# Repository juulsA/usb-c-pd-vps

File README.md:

# USB-C-PD-VPS

- variable powersupply driven by USB-PD 
- modular, up to 4 channels
- each channel is isolated
- output voltage 0 - 32V
  - resolution 0.5mV/step
  - voltage correction via sensing pins up to 1V above internally set output voltage
- current sense
  - "fuse" mode
  - current limiting mode
- remote control via USB

## Power Supply Channel Concept

## STM32 Pinout

| Pin Number | Pin Name | Net Name | Description |
| -------- | ------- | ------- | ------- |
| 1 | PB9 | - | - |
| 2 | PC14 | OSCX_IN | - |
| 3 | PC14 | OSCX_OUT | - |
| 4 | VDD | - | - |
| 5 | VSS | - | - |
| 6 | PF2 | NRST | hardware reset |
| 7  | PA0 | ADC0 | secondary side voltage monitoring |
| 8 | PA1 | - | - |
| 9 | PA2 | - | - |
| 10 | PA3 | ADC_SPI_NSS | adc chip select |
| 11 | PA4 | DAC_SPI_NSS | dac chip select |
| 12 | PA5 | STM32_SPI_SCK | spi clock |
| 13 | PA6 | STM32_SPI_MISO | master input/slave output |
| 14 | PA7 | STM32_SPI_MOSI | master output/slave input |
| 15 | PB0 | - | -|
| 16 | PB1 | - | -|
| 17 | PB2 | - | - |
| 18 | PA8 | - | - |
| 19 | PA9 | STM32_UART_TX | uart for controlling/programming |
| 20 | PC6 | - | - |
| 21 | PA10 | STM32_UART_RX | uart for controlling/programming |
| 22 | PA11 | - | - |
| 23 | PA12 | - | - |
| 24 | PA13 | SWDIO | - |
| 25 | PA14 | SWCLK/BOOT0 | enable stm bootloader |
| 26 | PA15 | STM32_TIM1_CH1_PWM | setting preregulator voltage |
| 27 | PB3 | DISABLE_VOLTAGE_SENSING | the external sense pins are not considered in output voltage adjustment  |
| 28 | PB4 | FUSE/#CURRENT_LIMITING_MODE | output is disabled, if an overcurrent event occurs or current is limited by reducing output voltage |
| 29 | PB5 | FPWM/#PFM | fixed frequency or phase frequency mode |
| 30 | PB6 | ENABLE_PWR_SPL | enable switching regulator |
| 31 | PB7 | PG | power good of switching regulator |
| 32 | PB8 | ENABLE_OUTPUT | voltage is applied to the output pins |

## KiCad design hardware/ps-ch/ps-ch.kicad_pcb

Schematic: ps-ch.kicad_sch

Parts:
C1, C4, C5, C8, C16, C17, C18, C25, C26, C27, C28, C29, C30, C33: 0.1μF 0603 100Vdc X7R ±20%; C_0603_1608Metric; Manufacturer Part Number GRM188R72A104MA35
C2, C9: 10pF 0603 100Vdc C0G ±5%; C_0603_1608Metric; Manufacturer Part Number GCM1885C2A100JA16
C3, C10, C12, C13, C14, C15, C19, C20, C21, C22: 10μF 1210 100Vdc X7S ±20%; C_1210_3225Metric; Manufacturer Part Number GRM32EC72A106ME05
C6, C7: 0.1μF 0603 100Vdc X7R ±20%; C_0805_2012Metric; Manufacturer Part Number GRM21BR61H106ME43
C11, C23: 39µF; CP_Elec_8x11.9; Manufacturer Part Number 875075855005
C24: 1μF 0603 16Vdc X7R ±20%; C_0603_1608Metric; Manufacturer Part Number GCM188R71C105MA49
C31, C32: 10μF 0805 50Vdc X5R ±20%; C_0805_2012Metric; Manufacturer Part Number GRM21BR61H106ME43
D1: PMEG60T30ELR; Nexperia_CFP3_SOD-123W; Manufacturer Part Number PMEG60T30ELRX
H1, H2, H3, H4: MountingHole_Pad; MountingHole_3.2mm_M3_Pad
J1, J3: 09652028; Manufacturer Part Number 09652028
J2, J4: Conn_02x12_Odd_Even; PinHeader_2x12_P2.54mm_Vertical
K1: TX2SA-3V; ATX203SA; Manufacturer Part Number TX2SA-3V
L1, L7: 60Ω@100MHz; L_0603_1608Metric; Manufacturer Part Number 74279228600
L2: 33µH; WE-LQS_6045; Manufacturer Part Number 74404064330
L3, L6: 100Ω@100MHz; WE-MPSB_2220; Manufacturer Part Number 74279224101
L4: 1µH; WE-HCI_5040; Manufacturer Part Number 744316100
L5: 2.6µH; WE-HCI_1890; Manufacturer Part Number 7443556260
Q1, Q2: BSS138; SOT-23
R1: 75kΩ 0603 0.1W ±1% ±100ppm/°C; R_0603_1608Metric; Manufacturer Part Number AC0603FR-0775KL
R2: 27kΩ 0603 0.1W ±0.1% ±25ppm/°C; R_0603_1608Metric; Manufacturer Part Number RT0603BRD0727KL
R3: 24kΩ 0603 0.1W ±1% ±100ppm/°C; R_0603_1608Metric; Manufacturer Part Number AC0603FR-0724KL; not fitted
R4: 24kΩ 0603 0.1W ±1% ±100ppm/°C; R_0603_1608Metric; Manufacturer Part Number AC0603FR-0724KL
R5: 3kΩ 0603 0.1W ±0.1% ±25ppm/°C; R_0603_1608Metric; Manufacturer Part Number RT0603BRD073KL
R6: 130kΩ 0603 0.1W ±0.1% ±25ppm/°C; R_0603_1608Metric; Manufacturer Part Number RT0603BRD07130KL
R7: 130kΩ 0603 0.1W ±0.1% ±25ppm/°C; R_0603_1608Metric; Manufacturer Part Number RT0603BRD07130KL; not fitted
R8, R9: 510Ω 1206 0.25W ±1% ±100ppm/°C; R_1206_3216Metric; Manufacturer Part Number AC1206FR-07510RL
R10: 0Ω 0603 0.1W ±1% ±100ppm/°C; R_0603_1608Metric; Manufacturer Part Number AC0603FR-070RL
R11: 4.7kΩ 0603 0.1W ±1% ±100ppm/°C; R_0603_1608Metric; Manufacturer Part Number AC0603FR-074k7L
R12: 10kΩ 0603 0.1W ±1% ±100ppm/°C; R_0402_1005Metric; Manufacturer Part Number AC0402FR-0710KL
R13, R21, R24: 10kΩ 0603 0.1W ±1% ±100ppm/°C; R_0603_1608Metric; Manufacturer Part Number AC0603FR-0710KL
R14: 7.15kΩ 0603 0.1W ±0.1% ±25ppm/°C; R_0603_1608Metric; Manufacturer Part Number RT0603BRD077K15L
R15: 7.15kΩ 0603 0.1W ±0.1% ±25ppm/°C; R_0603_1608Metric; Manufacturer Part Number RT0603BRD077K15L; not fitted
R16: 10kΩ 0603 0.1W ±0.1% ±25ppm/°C; R_0603_1608Metric; Manufacturer Part Number RT0603BRD0710KL
R17: 10kΩ 0603 0.1W ±0.1% ±25ppm/°C; R_0603_1608Metric; Manufacturer Part Number RT0603BRD0710KL; not fitted
R18, R25: 10kΩ 0402 0.063W ±1% ±100ppm/°C; R_0402_1005Metric; Manufacturer Part Number AC0402FR-0710KL
R19, R20: 0Ω 0402 0.063W ±1% ±100ppm/°C; R_0402_1005Metric; Manufacturer Part Number AC0402FR-070RL
R22, R23: 22Ω 0402 0.063W ±1% ±100ppm/°C; R_0402_1005Metric; Manufacturer Part Number AC0402FR-0722RL
U1: LMR51610X; SOT-23-6
U2: LM61495; VQFN-HR(16); Manufacturer Part Number LM61495RPHR
U3, U4: ADuM1401xRW; SOIC-16W_7.5x10.3mm_P1.27mm
U5: OPA992IDBVR; SOT-23-5; Manufacturer Part Number OPA992IDBVR

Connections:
3V3: C25.2, C29.2, J2.1, J2.4, J4.1, J4.4, R21.2, U3.10 (VE2), U3.16 (VDD2), U4.1 (VDD1), U4.7 (VE1)
+3V3: C2.2, C5.2, C6.2, C7.2, C26.2, C27.2, C28.2, C30.2, D1.1 (K), K1.1, L2.1, R1.1, R12.1, U2.5 (BIAS), U3.1 (VDD1), U3.7 (VE1), U4.10 (VE2), U4.16 (VDD2); also elsewhere on the board
/AIN0: R2.1, R5.2; also elsewhere on the board
/Current Measurement/IN: C23.1, L3.1, L6.1, R8.2, R9.2; also elsewhere on the board
/DAC/VOUTA: U5.3 (+); also elsewhere on the board
/DISCHARGE: Q1.1 (G), R25.2; also elsewhere on the board
/EN_PWR_SPL: R18.2, U2.13 (EN); also elsewhere on the board
/Flyback Converter/V_PREREG_EQUIV_PWM: U3.14 (VOA); also elsewhere on the board
/PG: R12.2, U2.10 (~RESET); also elsewhere on the board
/STM32/EN_EXT_VSENSE: Q2.1 (G); also elsewhere on the board
/STM32/STM32_TIM1_CH1_PWM: U3.3 (VIA); also elsewhere on the board
/STM32/STM32_UART_RX: R22.2; also elsewhere on the board
/STM32/STM32_UART_TX: U4.11 (VID); also elsewhere on the board
/STM32/SWCLK/BOOT0: U4.13 (VOB); also elsewhere on the board
/STM32/~STM32_RST: U4.14 (VOA); also elsewhere on the board
/Switch/ARM_OUTPUT: U3.6 (VOD); also elsewhere on the board
/Voltage Correction/VFB: R6.2, R7.2, R11.2, R14.2, R15.2, R16.2, R17.1, U2.7 (FB); also elsewhere on the board
/Voltage Correction/VSENSE+: K1.4; also elsewhere on the board
/Voltage Correction/VSENSE-: K1.9; also elsewhere on the board
ACTIVATE_BOOTLOADER: J2.5, J4.5, R24.2, U4.4 (VIB)
ARM_OUTPUT: R13.2, U3.11 (VID)
Earth: C25.1, C29.1, H1.1, H2.1, H3.1, H4.1, J1.2, J2.2, J2.3, J2.6, J2.7, J2.10, J2.11, J2.14, J2.15, J2.18, J2.19, J2.22, J2.23, J3.2, J4.2, J4.3, J4.6, J4.7, J4.10, J4.11, J4.14, J4.15, J4.18, J4.19, J4.21, J4.22, J4.23, J4.24, R13.1, R24.1, U3.9 (GND2), U3.15 (GND2), U4.2 (GND1), U4.8 (GND1); also elsewhere on the board
GND: C3.1, C4.1, C5.1, C6.1, C7.1, C10.1, C11.2, C12.1, C13.1, C14.1, C15.1, C16.1, C17.1, C18.1, C19.1, C20.1, C21.1, C22.1, C23.2, C24.1, C26.1, C27.1, C28.1, C30.1, C31.1, C32.1, C33.1, K1.10, Q1.2 (S), Q2.2 (S), R3.2, R4.2, R5.1, R14.1, R15.1, R18.1, R19.2, R20.1, R25.1, U1.2 (GND), U2.1 (PGND2), U2.8 (AGND), U2.15 (PGND1), U3.2 (GND1), U3.8 (GND1), U4.9 (GND2), U4.15 (GND2), U5.2 (V-); also elsewhere on the board
NRST: J2.8, J4.8, R21.1, U4.3 (VIA)
unnamed: C9.1, R11.1
unnamed: C9.2, C18.2, C19.2, C20.2, C21.2, C22.2, L3.2, L5.1, L6.2, R6.1, R7.1
unnamed: D1.2 (A), K1.12, Q2.3 (D)
unnamed: Q1.3 (D), R8.1, R9.1
unnamed: C1.1, U1.1 (CB)
unnamed: C3.2, C4.2, L1.1, U1.4 (EN), U1.5 (VIN)
unnamed: C2.1, R1.2, R3.1, R4.1, U1.3 (FB)
unnamed: C1.2, L2.2, U1.6 (SW)
unnamed: C8.1, R10.1, U2.4 (CBOOT)
unnamed: R10.2, U2.3 (RBOOT)
unnamed: R20.2, U2.9 (RT)
unnamed: R19.1, U2.11 (SPSP)
unnamed: C8.2, L5.2, U2.16 (SW)
unnamed: C24.2, U2.6 (VCC), U2.12 (SYNC/MODE)
unnamed: C11.1, C12.2, C13.2, C14.2, C15.2, C16.2, C17.2, L4.1, U2.2 (VIN2), U2.14 (VIN1)
unnamed: R22.1, U4.12 (VOC)
unnamed: R23.2, U4.6 (VOD)
unnamed: R16.1, R17.2, U5.1, U5.4 (-)
unnamed: C32.2, C33.2, L7.1, U5.5 (V+)
PRI_HI: J1.1, J3.1; also elsewhere on the board
UART0_RX: J2.12, R23.1
UART0_TX: J2.9, U4.5 (VIC)
UART1_RX: J2.16, J4.12
UART1_TX: J2.13, J4.9
UART2_RX: J2.20, J4.16
UART2_TX: J2.17, J4.13
UART3_RX: J2.24, J4.20
UART3_TX: J2.21, J4.17
VDC: C10.2, C31.2, L1.2, L4.2, L7.2; also elsewhere on the board
VOUT: K1.3, R2.2; also elsewhere on the board
VSENSE+: K1.5
VSENSE-: K1.8

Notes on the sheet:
7.6uF@5V(-20%) 3uF@35V(-20%)
programmable current limit
INPUT
OPAMP POWER SUPPLY
OUTPUT
5V to 35V
-connect RT(9) to GND for 2.2MHz operation -connect SYNC/MODE(12) to VCC for FPWM -connect SPSP to GND to disable spread-spectrum
0V to 32V
ADC CH0

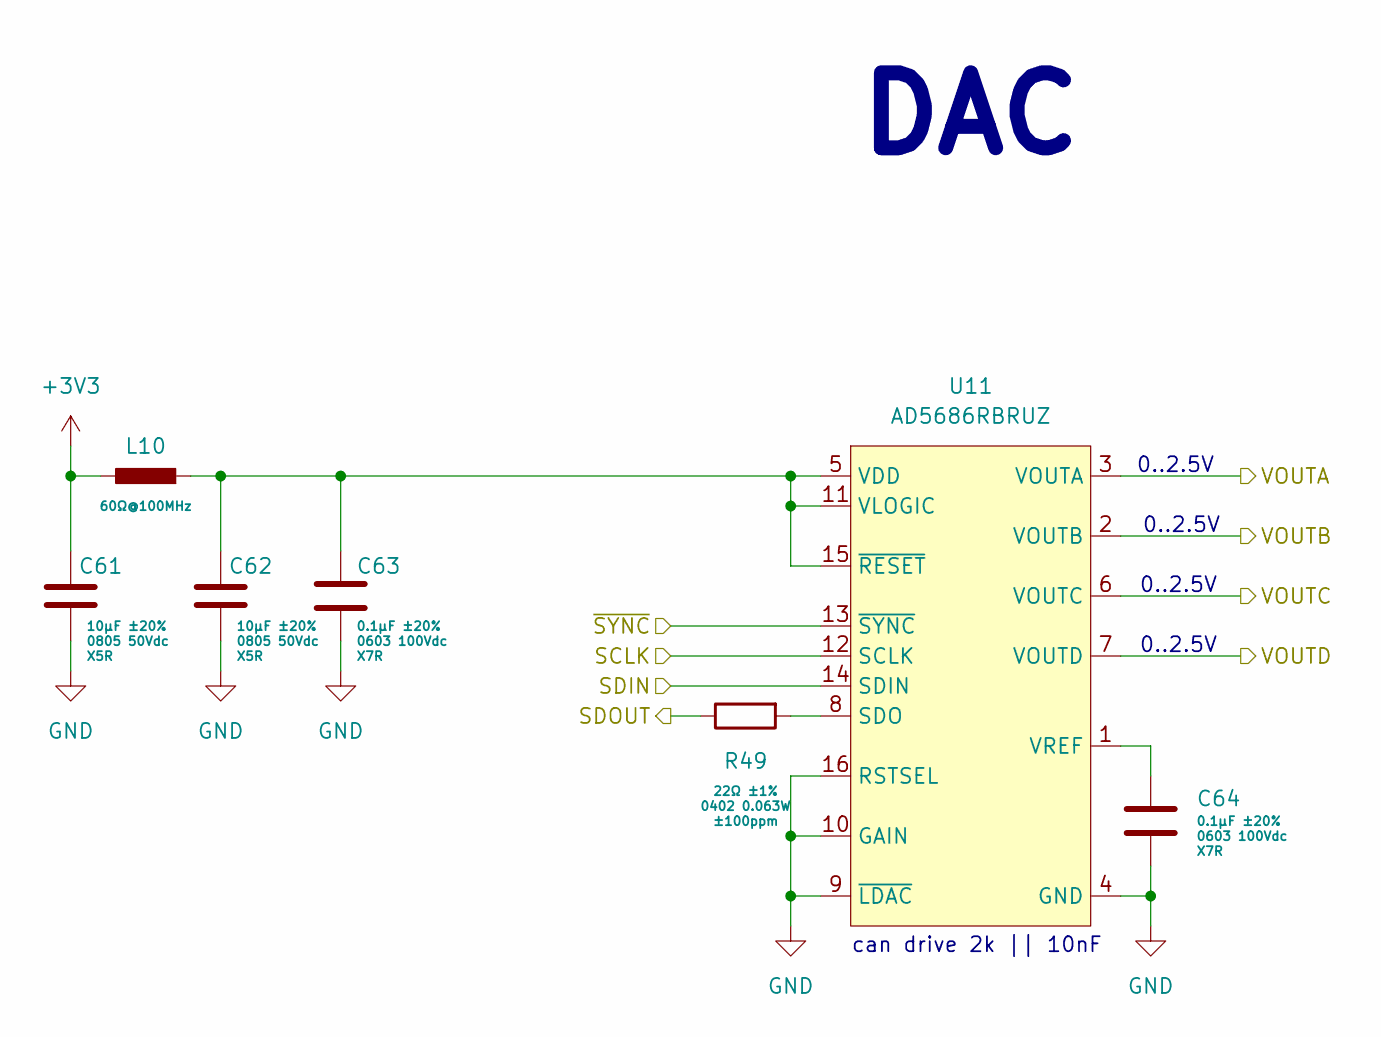
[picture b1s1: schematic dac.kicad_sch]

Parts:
C61, C62: 10μF 0805 50Vdc X5R ±20%; C_0805_2012Metric; Manufacturer Part Number GRM21BR61H106ME43
C63, C64: 0.1μF 0603 100Vdc X7R ±20%; C_0603_1608Metric; Manufacturer Part Number GRM188R72A104MA35
L10: 60Ω@100MHz; L_0603_1608Metric; Manufacturer Part Number 74279228600
R49: 22Ω 0402 0.063W ±1% ±100ppm/°C; R_0402_1005Metric; Manufacturer Part Number AC0402FR-0722RL
U11: AD5686RBRUZ; TSSOP-16_4.4x5mm_P0.65mm; Manufacturer Part Number AD5686RBRUZ-RL7

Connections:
+3V3: C61.2, L10.2; also elsewhere on the board
/ADC_REF: U11.7 (VOUTD); also elsewhere on the board
/Current Measurement/LIMIT: U11.6 (VOUTC); also elsewhere on the board
/DAC/VOUTA: U11.3 (VOUTA); also elsewhere on the board
/DAC/VOUTB: U11.2 (VOUTB); also elsewhere on the board
/MISO: R49.1; also elsewhere on the board
/MOSI: U11.14 (SDIN); also elsewhere on the board
/SCK: U11.12 (SCLK); also elsewhere on the board
/~DAC_CS: U11.13 (~SYNC); also elsewhere on the board
GND: C61.1, C62.1, C63.1, C64.1, U11.4 (GND), U11.9 (~LDAC), U11.10 (GAIN), U11.16 (RSTSEL); also elsewhere on the board
unnamed: R49.2, U11.8 (SDO)
unnamed: C62.2, C63.2, L10.1, U11.5 (VDD), U11.11 (VLOGIC), U11.15 (~RESET)
unnamed: C64.2, U11.1 (VREF)

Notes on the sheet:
0..2.5V
DAC
can drive 2k || 10nF

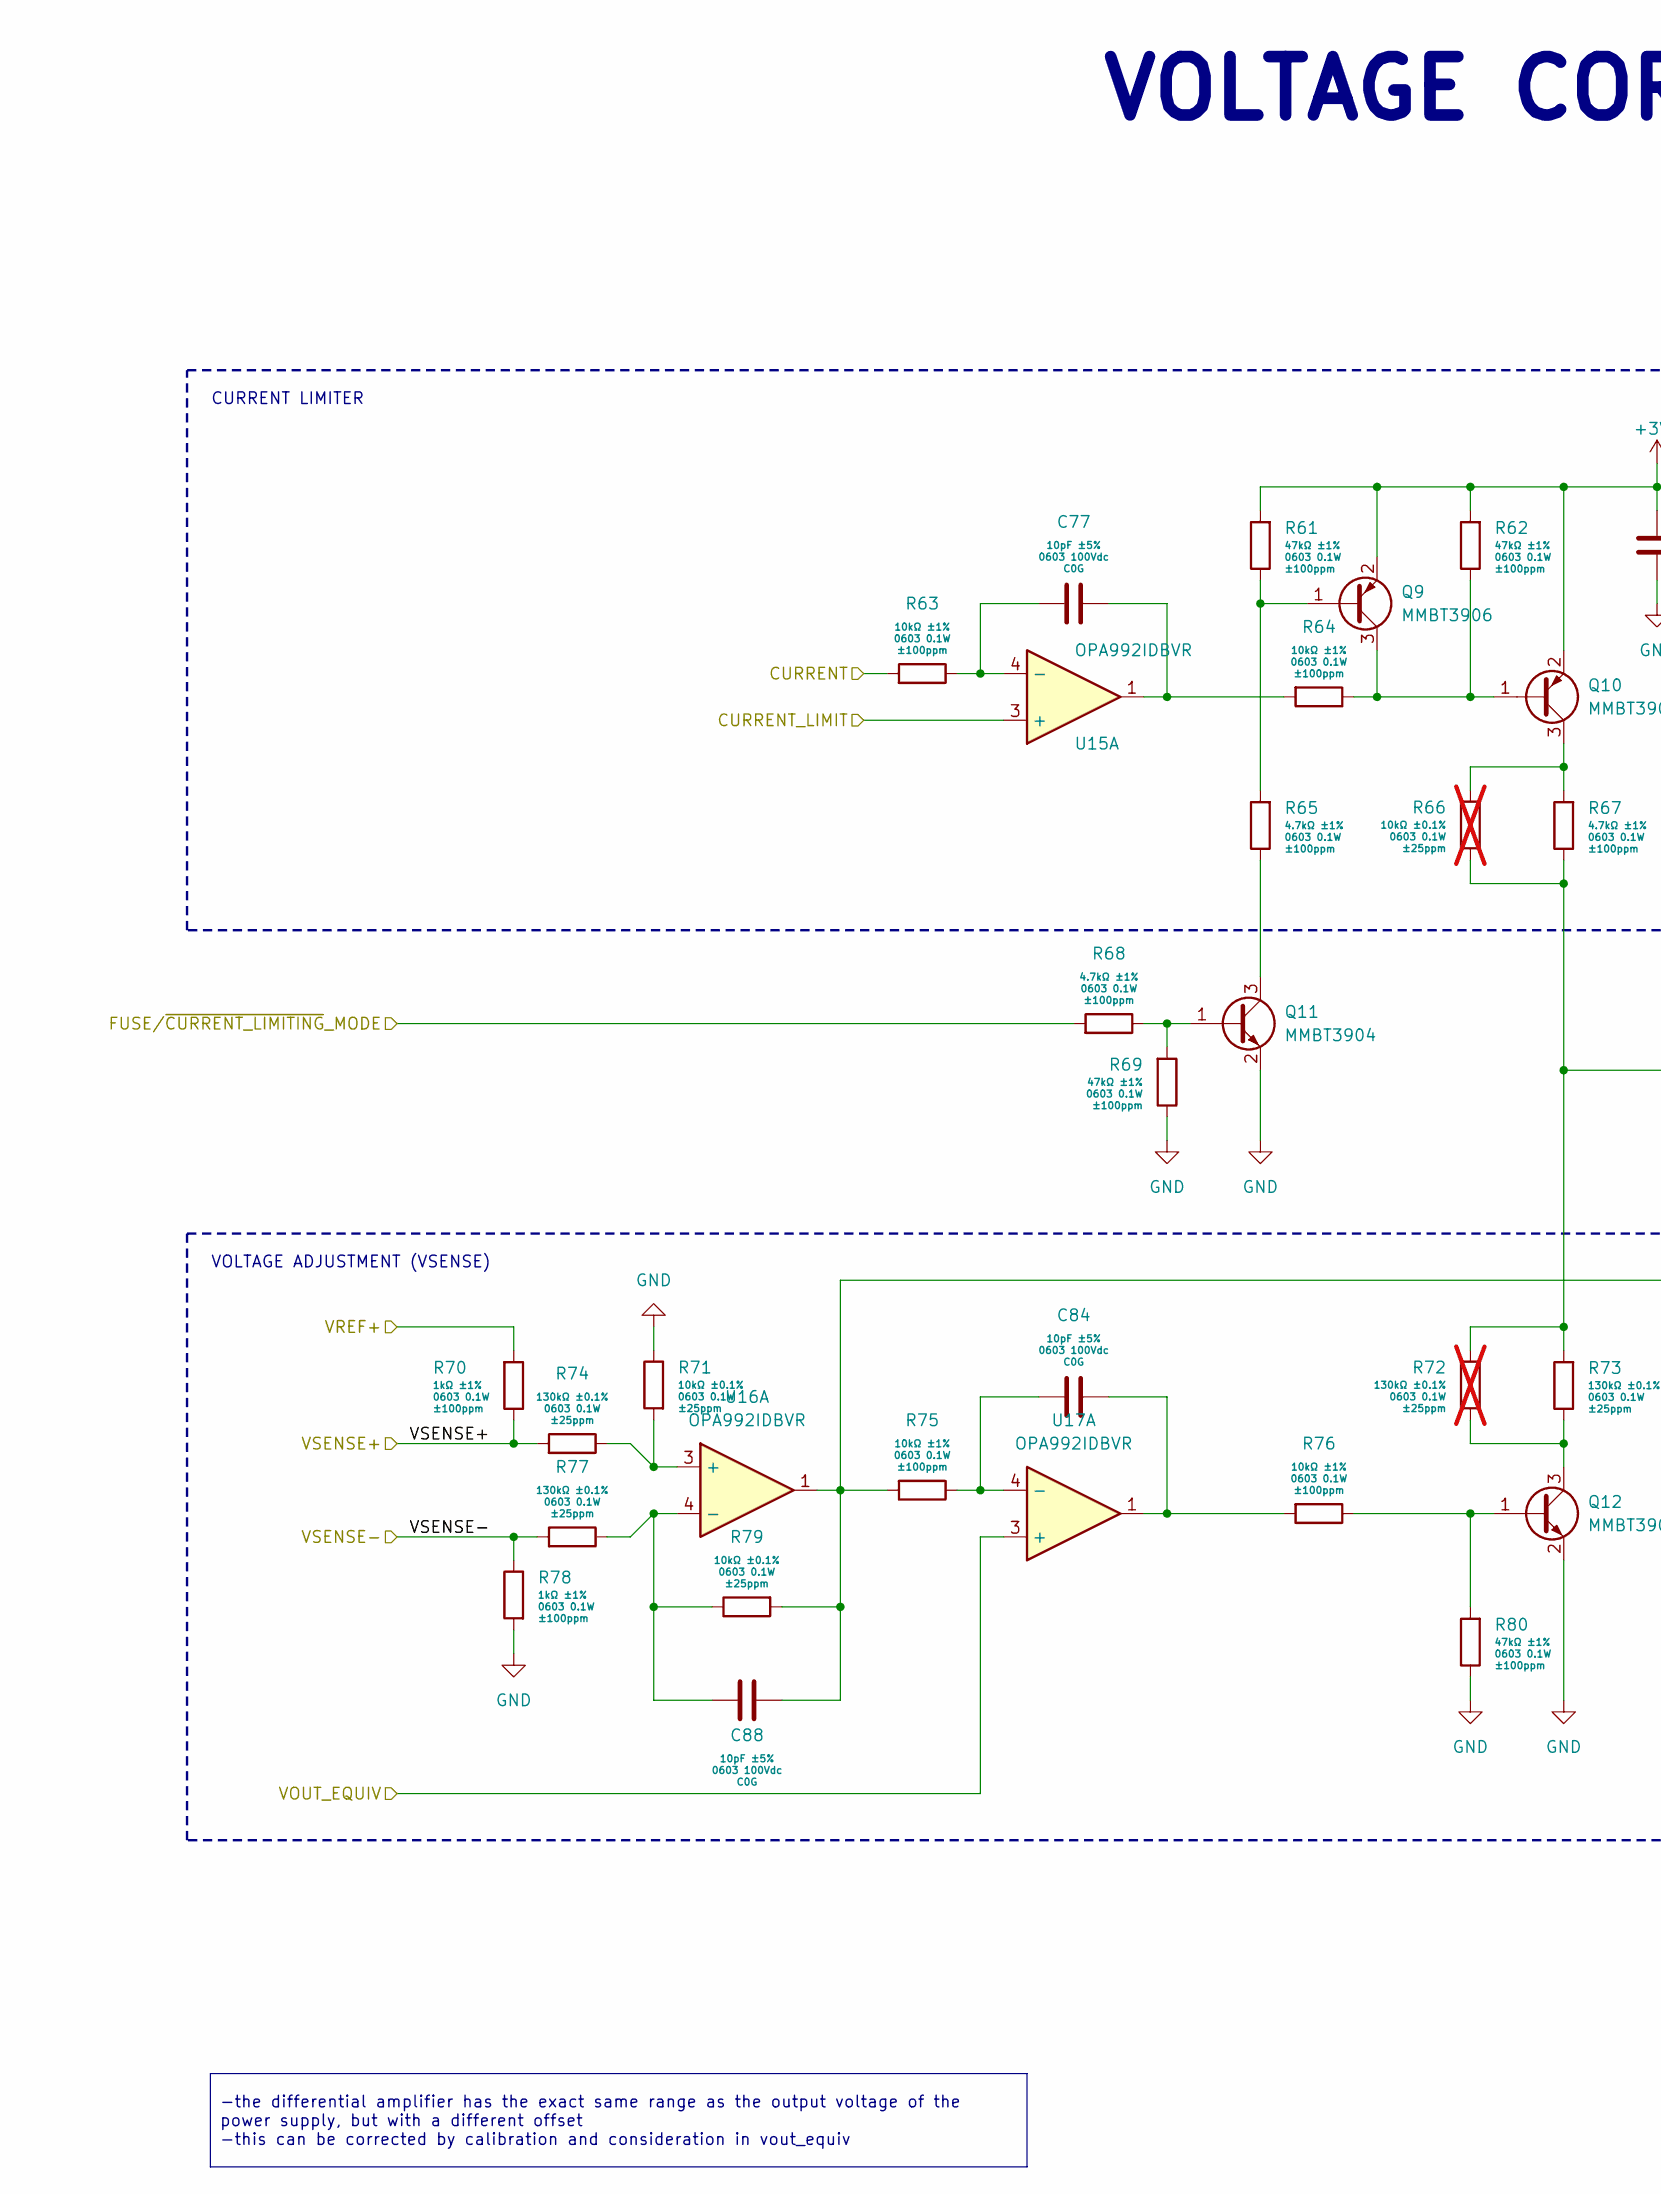
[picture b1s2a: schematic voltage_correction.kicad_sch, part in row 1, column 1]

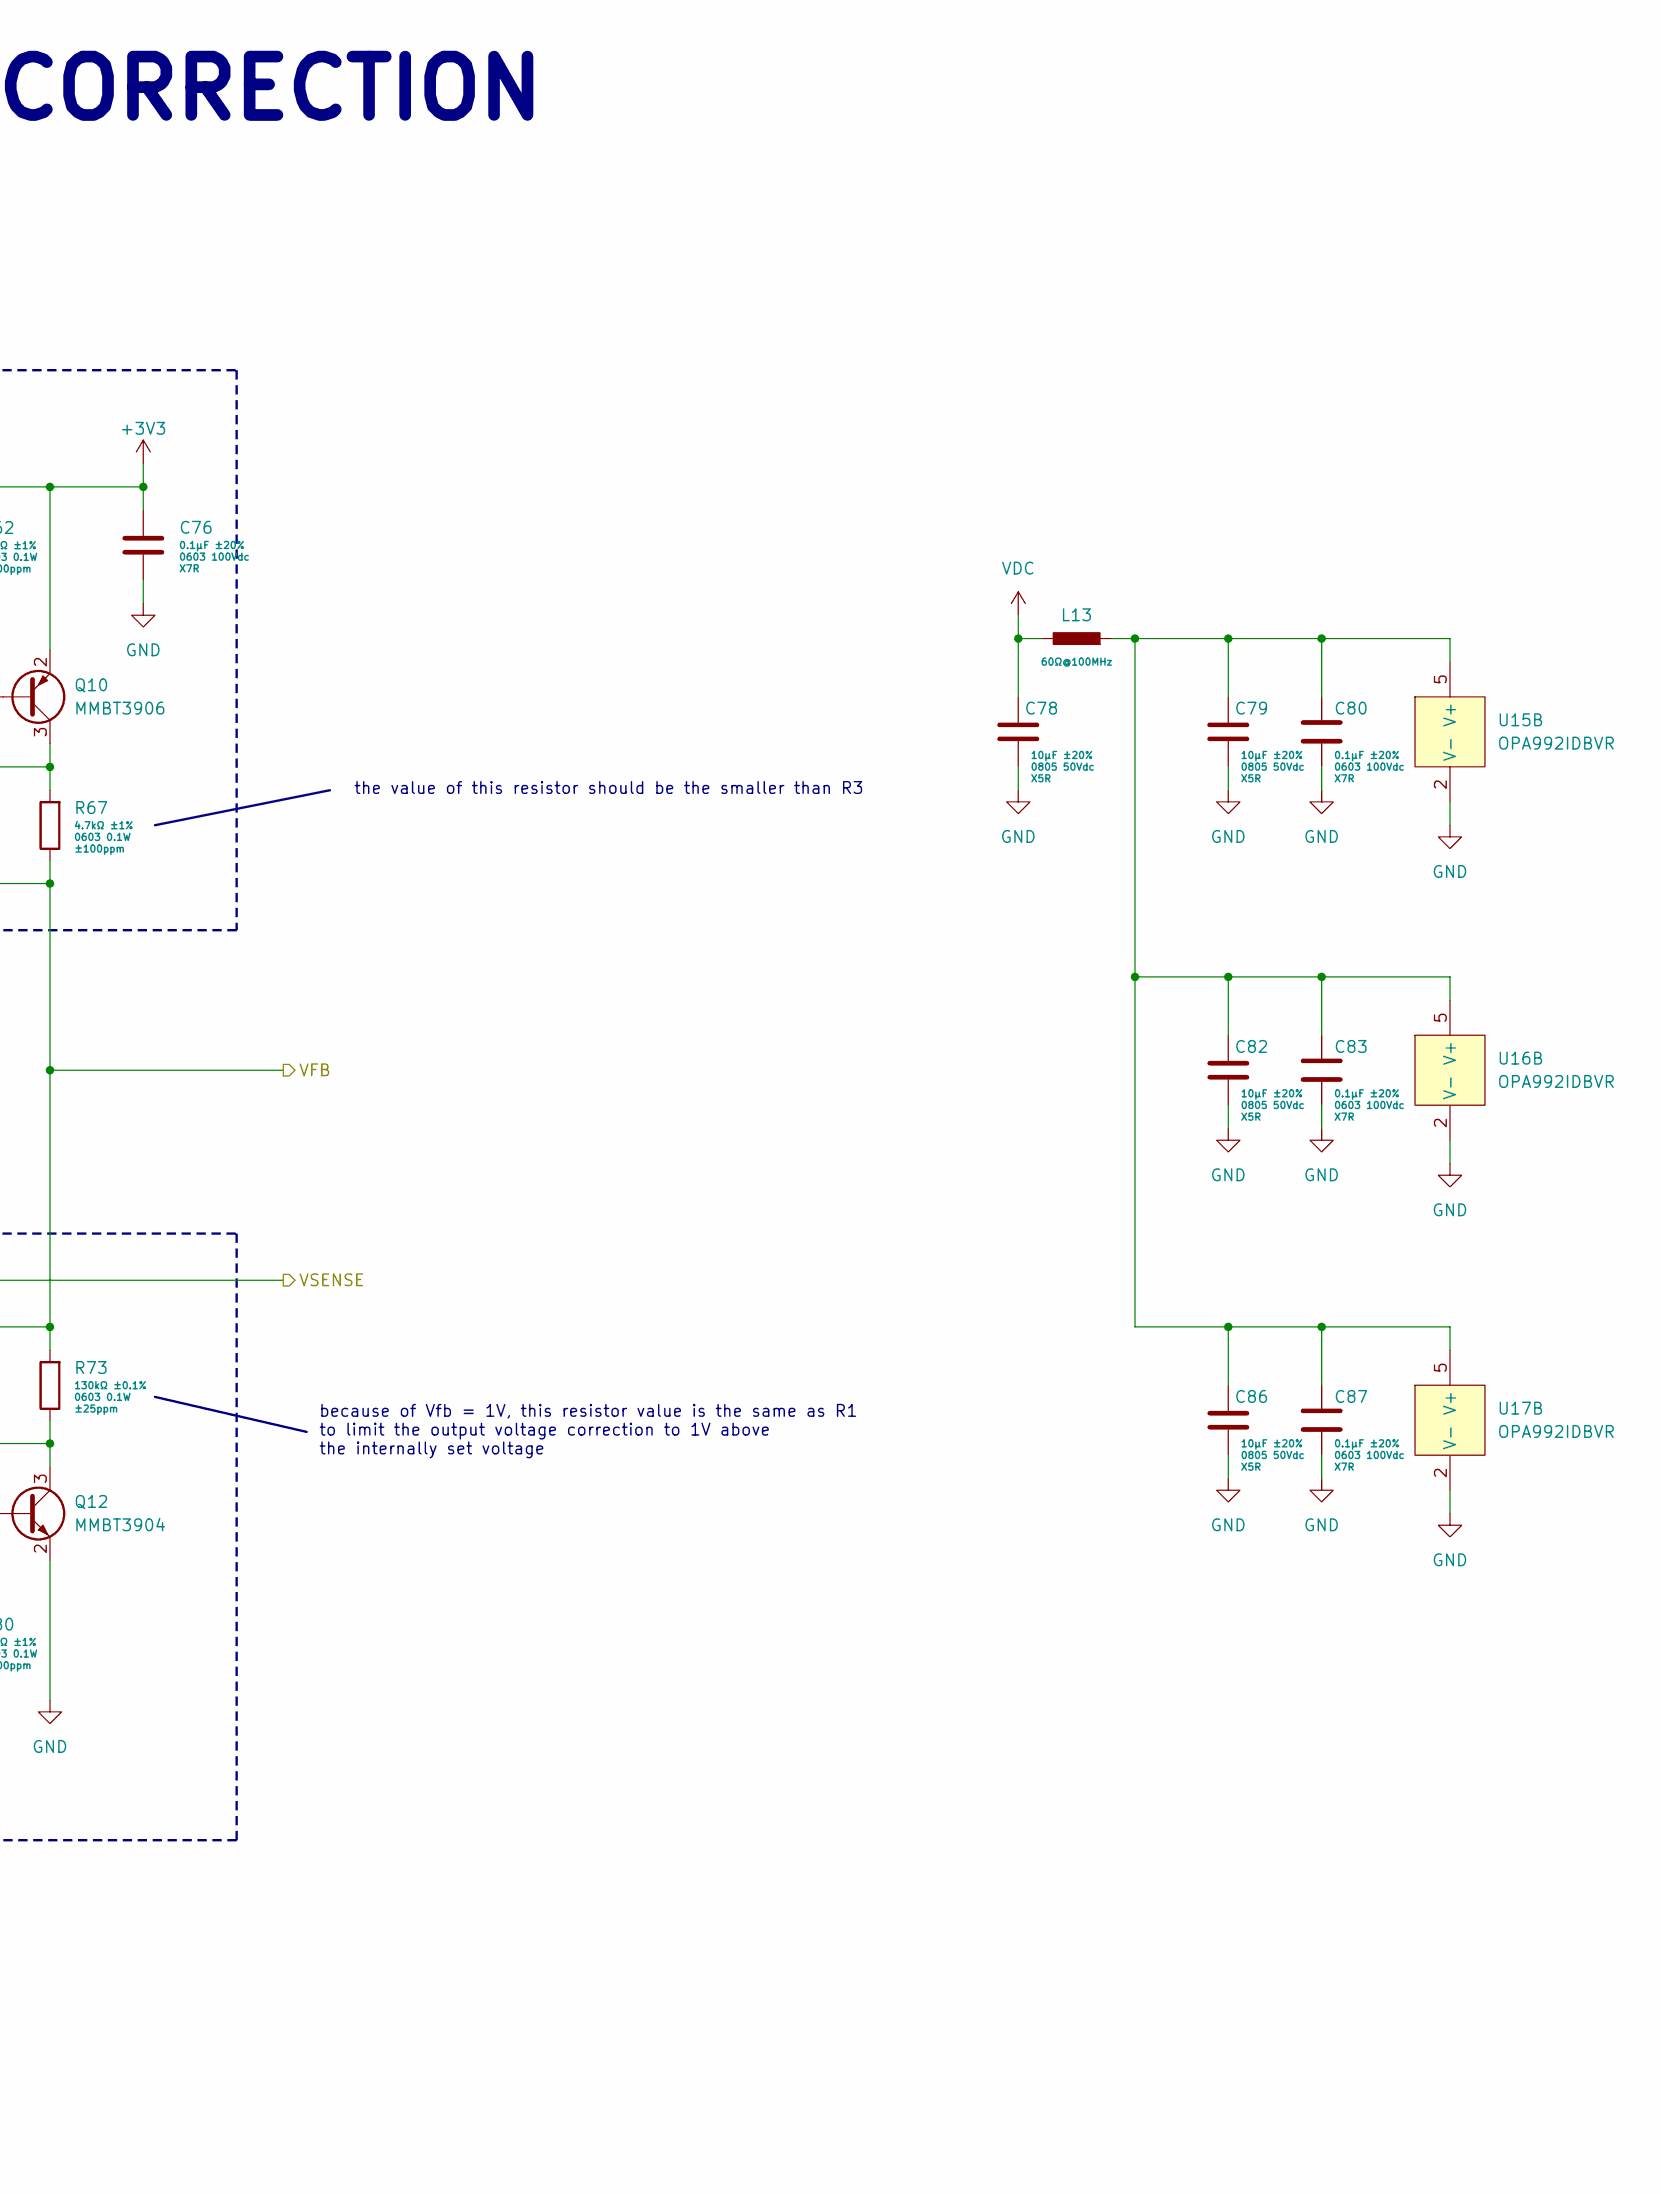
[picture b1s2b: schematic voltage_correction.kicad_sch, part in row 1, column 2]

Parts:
C76, C80, C83, C87: 0.1μF 0603 100Vdc X7R ±20%; C_0603_1608Metric; Manufacturer Part Number GRM188R72A104MA35
C77, C84, C88: 10pF 0603 100Vdc C0G ±5%; C_0603_1608Metric; Manufacturer Part Number GCM1885C2A100JA16
C78, C79, C82, C86: 10μF 0805 50Vdc X5R ±20%; C_0805_2012Metric; Manufacturer Part Number GRM21BR61H106ME43
L13: 60Ω@100MHz; L_0603_1608Metric; Manufacturer Part Number 74279228600
Q9, Q10: MMBT3906; SOT-23
Q11, Q12: MMBT3904; SOT-23
R61, R62, R69, R80: 47kΩ 0603 0.1W ±1% ±100ppm/°C; R_0603_1608Metric; Manufacturer Part Number AC0603FR-0747L
R63, R64, R75, R76: 10kΩ 0603 0.1W ±1% ±100ppm/°C; R_0603_1608Metric; Manufacturer Part Number AC0603FR-0710KL
R65, R67, R68: 4.7kΩ 0603 0.1W ±1% ±100ppm/°C; R_0603_1608Metric; Manufacturer Part Number AC0603FR-074k7L
R66: 10kΩ 0603 0.1W ±0.1% ±25ppm/°C; R_0603_1608Metric; Manufacturer Part Number RT0603BRD0710KL; not fitted
R70, R78: 1kΩ 0603 0.1W ±1% ±100ppm/°C; R_0603_1608Metric; Manufacturer Part Number AC0603FR-071KL
R71, R79: 10kΩ 0603 0.1W ±0.1% ±25ppm/°C; R_0603_1608Metric; Manufacturer Part Number RT0603BRD0710KL
R72: 130kΩ 0603 0.1W ±0.1% ±25ppm/°C; R_0603_1608Metric; Manufacturer Part Number RT0603BRD07130KL; not fitted
R73, R74, R77: 130kΩ 0603 0.1W ±0.1% ±25ppm/°C; R_0603_1608Metric; Manufacturer Part Number RT0603BRD07130KL
U15, U16, U17: OPA992IDBVR; SOT-23-5; Manufacturer Part Number OPA992IDBVR

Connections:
+3V3: C76.2, Q9.2 (E), Q10.2 (E), R61.2, R62.2; also elsewhere on the board
/ADC/AIN1: C88.1, R75.2, R79.2, U16.1; also elsewhere on the board
/AIN2: R63.2; also elsewhere on the board
/Current Measurement/LIMIT: U15.3 (+); also elsewhere on the board
/Current Measurement/RESET: R68.2; also elsewhere on the board
/DAC/VOUTB: U17.3 (+); also elsewhere on the board
/Voltage Correction/VFB: R66.2, R67.1, R72.1, R73.2; also elsewhere on the board
/Voltage Correction/VSENSE+: R70.1, R74.2; also elsewhere on the board
/Voltage Correction/VSENSE-: R77.2, R78.1; also elsewhere on the board
GND: C76.1, C78.1, C79.1, C80.1, C82.1, C83.1, C86.1, C87.1, Q11.2 (E), Q12.2 (E), R69.1, R71.1, R78.2, R80.1, U15.2 (V-), U16.2 (V-), U17.2 (V-); also elsewhere on the board
unnamed: C77.1, R64.2, U15.1
unnamed: C84.2, R76.2, U17.1
unnamed: Q9.1 (B), R61.1, R65.2
unnamed: Q9.3 (C), Q10.1 (B), R62.1, R64.1
unnamed: Q10.3 (C), R66.1, R67.2
unnamed: Q11.1 (B), R68.1, R69.2
unnamed: Q11.3 (C), R65.1
unnamed: Q12.1 (B), R76.1, R80.2
unnamed: Q12.3 (C), R72.2, R73.1
unnamed: C77.2, R63.1, U15.4 (-)
unnamed: C79.2, C80.2, C82.2, C83.2, C86.2, C87.2, L13.1, U15.5 (V+), U16.5 (V+), U17.5 (V+)
unnamed: R71.2, R74.1, U16.3 (+)
unnamed: C88.2, R77.1, R79.1, U16.4 (-)
unnamed: C84.1, R75.1, U17.4 (-)
VDC: C78.2, L13.2; also elsewhere on the board
VOUT: R70.2; also elsewhere on the board

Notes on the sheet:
VOLTAGE ADJUSTMENT (VSENSE)
VOLTAGE CORRECTION
because of Vfb = 1V, this resistor value is the same as R1 to limit the output voltage correction to 1V above the internally set voltage
CURRENT LIMITER
the value of this resistor should be the smaller than R3
-the differential amplifier has the exact same range as the output voltage of the power supply, but with a different offset -this can be corrected by calibration and consideration in vout_equiv

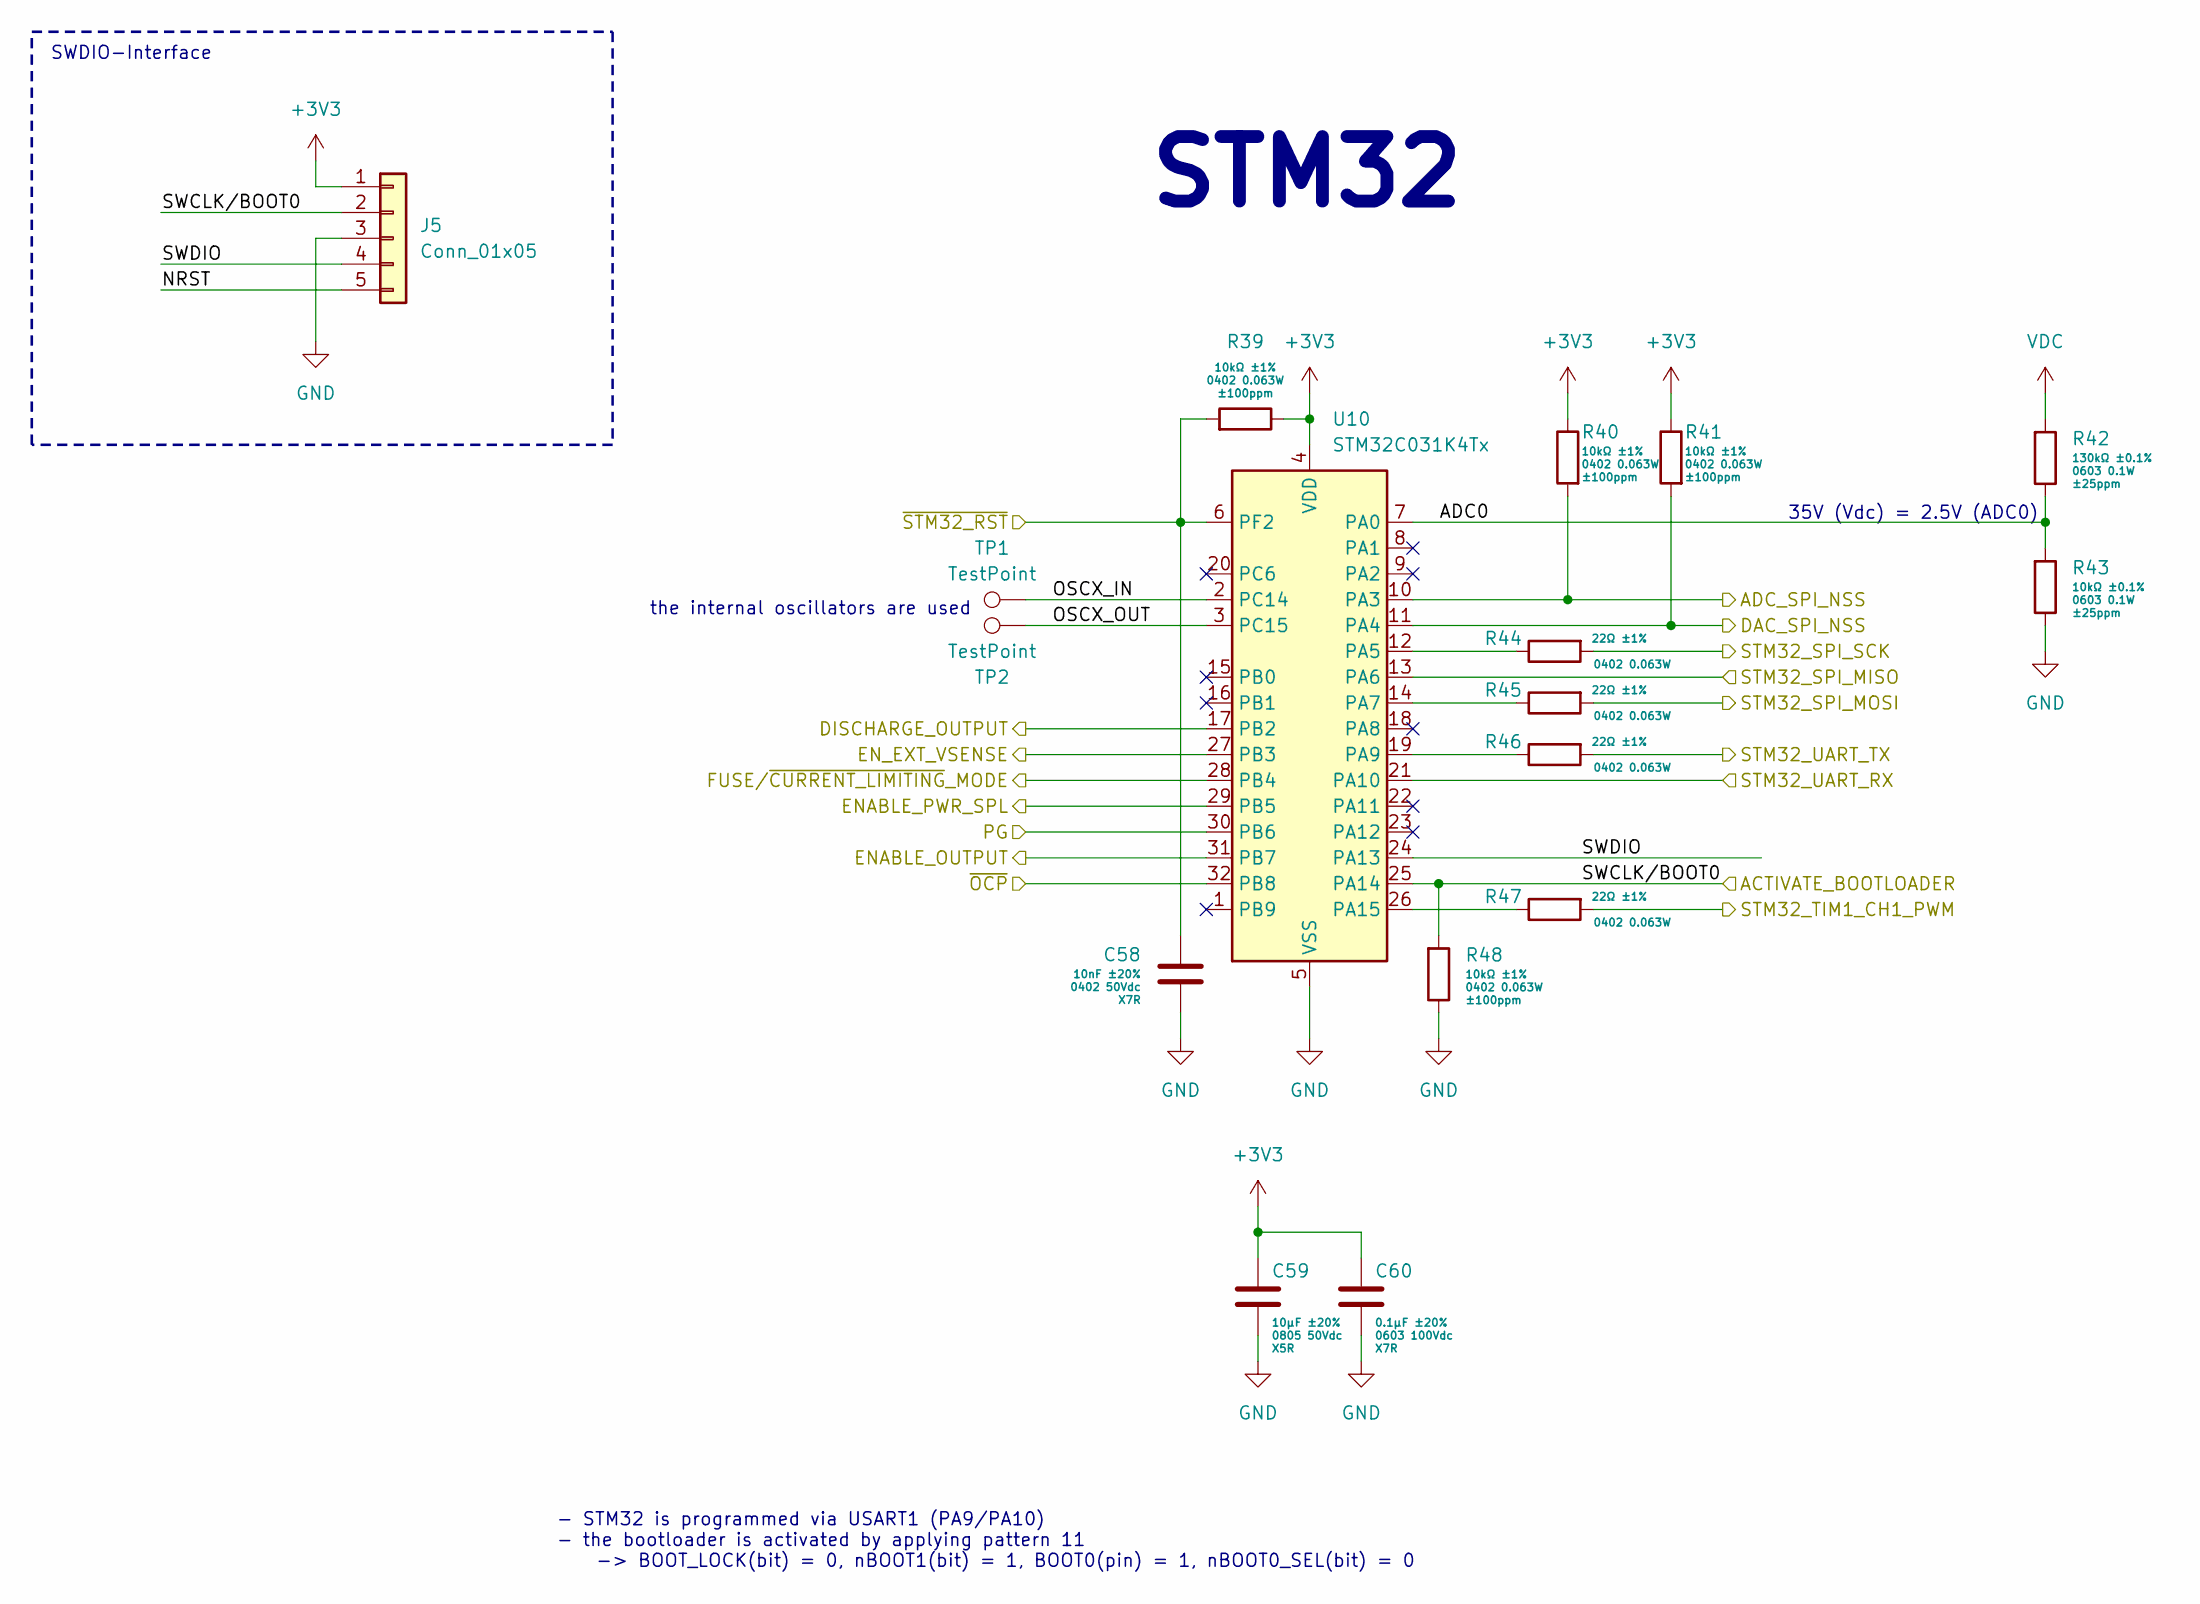
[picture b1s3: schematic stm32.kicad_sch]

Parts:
C58: 10nF 0402 50Vdc X7R ±20%; C_0402_1005Metric; Manufacturer Part Number GRM155R71H103MA88
C59: 10μF 0805 50Vdc X5R ±20%; C_0805_2012Metric; Manufacturer Part Number GRM21BR61H106ME43
C60: 0.1μF 0603 100Vdc X7R ±20%; C_0603_1608Metric; Manufacturer Part Number GRM188R72A104MA35
J5: Conn_01x05; PinHeader_1x05_P2.54mm_Vertical
R39, R40, R41, R48: 10kΩ 0402 0.063W ±1% ±100ppm/°C; R_0402_1005Metric; Manufacturer Part Number AC0402FR-0710KL
R42: 10kΩ 0402 0.063W ±1% ±100ppm/°C; R_0603_1608Metric; Manufacturer Part Number RT0603BRD07130KL
R43: 10kΩ 0402 0.063W ±1% ±100ppm/°C; R_0603_1608Metric; Manufacturer Part Number RT0603BRD0710KL
R44, R45, R46, R47: 22Ω 0402 0.063W ±1% ±100ppm/°C; R_0402_1005Metric; Manufacturer Part Number AC0402FR-0722RL
TP1, TP2: TestPoint; TestPoint_Pad_D1.0mm
U10: STM32C031K4Tx; LQFP-32_7x7mm_P0.8mm

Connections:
+3V3: C59.2, C60.2, J5.1, R39.1, R40.1, R41.1, U10.4 (VDD); also elsewhere on the board
/Current Measurement/RESET: U10.28 (PB4); also elsewhere on the board
/DISCHARGE: U10.17 (PB2); also elsewhere on the board
/EN_OUTPUT: U10.31 (PB7); also elsewhere on the board
/EN_PWR_SPL: U10.29 (PB5); also elsewhere on the board
/MISO: U10.13 (PA6); also elsewhere on the board
/MOSI: R45.2; also elsewhere on the board
/PG: U10.30 (PB6); also elsewhere on the board
/SCK: R44.2; also elsewhere on the board
/STM32/ADC0: R42.1, R43.2, U10.7 (PA0)
/STM32/EN_EXT_VSENSE: U10.27 (PB3); also elsewhere on the board
/STM32/NRST: J5.5
/STM32/OSCX_IN: TP1.1, U10.2 (PC14)
/STM32/OSCX_OUT: TP2.1, U10.3 (PC15)
/STM32/STM32_TIM1_CH1_PWM: R47.2; also elsewhere on the board
/STM32/STM32_UART_RX: U10.21 (PA10); also elsewhere on the board
/STM32/STM32_UART_TX: R46.2; also elsewhere on the board
/STM32/SWCLK/BOOT0: J5.2, R48.2, U10.25 (PA14); also elsewhere on the board
/STM32/SWDIO: J5.4, U10.24 (PA13)
/STM32/~STM32_RST: C58.2, R39.2, U10.6 (PF2); also elsewhere on the board
/~ADC_CS: R40.2, U10.10 (PA3); also elsewhere on the board
/~DAC_CS: R41.2, U10.11 (PA4); also elsewhere on the board
/~OCP: U10.32 (PB8); also elsewhere on the board
GND: C58.1, C59.1, C60.1, J5.3, R43.1, R48.1, U10.5 (VSS); also elsewhere on the board
unnamed: R44.1, U10.12 (PA5)
unnamed: R45.1, U10.14 (PA7)
unnamed: R46.1, U10.19 (PA9)
unnamed: R47.1, U10.26 (PA15)
VDC: R42.2; also elsewhere on the board

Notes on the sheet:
35V (Vdc) = 2.5V (ADC0)
the internal oscillators are used
SWDIO-Interface
STM32
- STM32 is programmed via USART1 (PA9/PA10) - the bootloader is activated by applying pattern 11 -> BOOT_LOCK(bit) = 0, nBOOT1(bit) = 1, BOOT0(pin) = 1, nBOOT0_SEL(bit) = 0
